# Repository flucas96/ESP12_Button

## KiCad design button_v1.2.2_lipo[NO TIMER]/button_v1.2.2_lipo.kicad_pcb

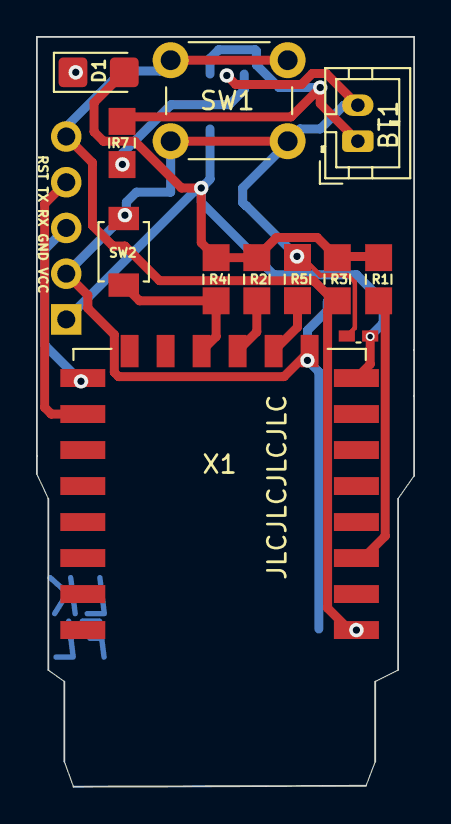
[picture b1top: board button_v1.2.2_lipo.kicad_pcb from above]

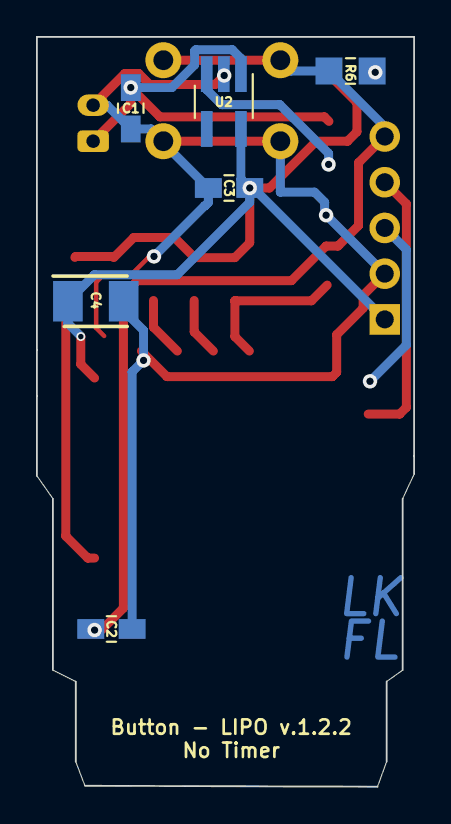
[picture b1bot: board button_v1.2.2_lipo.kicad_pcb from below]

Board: 2 copper layers, 21.0 x 41.7 mm, 19 parts (6 on the bottom side), 12 nets.

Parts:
BT1: Battery_Cell; JST_PH_B2B-PH-K_1x02_P2.00mm_Vertical
C1, C3: 10uF; C_0805_2012handsodermod
C2: 100nF; C_0805_2012handsodermod
C4: TAJB476M010TNJ; CAPPM3528X210N
C5: 100nF; C_0402_1005Metric_Pad0.74x0.62mm_HandSoldermod
D1: LED; LED_1206_3216Metric_Castellated
J1: Conn_01x05_Female; PinSocket_1x05_P2.54mm_Vertical_mod
R1, R2, R3, R4: 10k; R_0805_2012handsoldermod
R5: 4.7k; R_0805_2012handsoldermod
R6: 1k; R_0805_2012handsoldermod
R7: 100k; R_0805_2012handsoldermod
SW1: SW_Push; SW_PUSH_6mm_H8mm_mod
SW2: SW_Push; SW_SPST_B3U-1000P_mod
U2: AP2112K-3.3; SOT-23-5_HandSolderingmod
X1: ESP-12E

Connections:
/EN: R1.2, X1.3
/GND: BT1.2, C1.1, C2.1, C3.1, C4.2, C5.2, J1.2, R5.1, SW1.2, SW2.2, U2.2, X1.9
/GPIO0: R4.2, SW2.1, X1.12
/GPIO2: R2.2, X1.11
/GPIO15: R5.2, X1.10
/RST: C2.2, J1.5, R3.2, R6.2, SW1.1, X1.1
/RX: J1.3, X1.15
/TX: J1.4, X1.16
/VCC: C3.2, C4.1, C5.1, D1.2, J1.1, R1.1, R2.1, R3.1, R4.1, U2.5, X1.8
unnamed: BT1.1, C1.2, R7.2, U2.1
unnamed: D1.1, R6.1
unnamed: R7.1, U2.3
